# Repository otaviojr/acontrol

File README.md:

# acontrol
DIY Access Control Software - Fingerprint + NFC + Raspberry

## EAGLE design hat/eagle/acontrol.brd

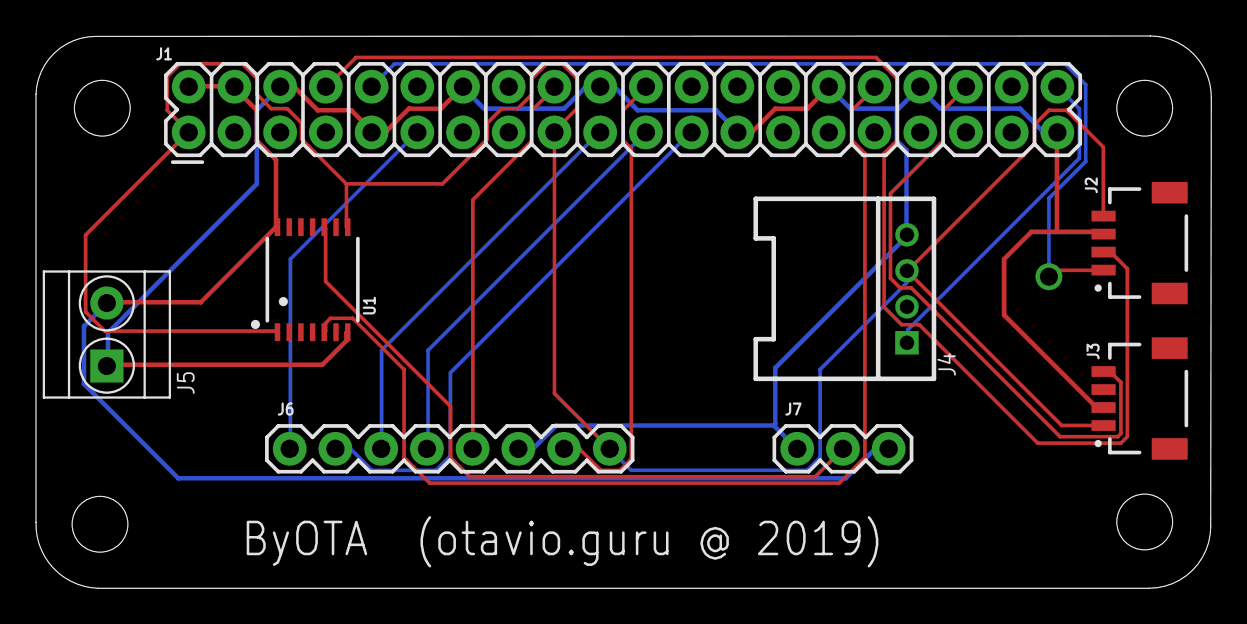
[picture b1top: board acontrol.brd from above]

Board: 2 copper layers, 65.3 x 30.7 mm, 8 parts (0 on the bottom side), 15 nets.

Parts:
J1: RASPBERRYPI-40-PIN-GPIO_PTH_NO_SHROUD; 2X20
J2, J3: JST04_1MM_RA
J4: 4P-2.0-90D; HW4-2.0-90D
J5: GREEN-2P-3.5; H2-3.5-7.0X7.0MM
J6: 1X08
J7: 455-1750-1-ND; 1X03
U1: TXB0104; TSSOP14

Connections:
3.3V: J1.1, J1.17, J2.4, J3.1, J4.3, J6.8, U1.1, U1.8
5V: J1.2, J1.4, J5.2, J7.3, U1.14
BUZZER_IN: J1.40, J4.1
GND: J1.6, J1.9, J1.14, J1.20, J1.25, J1.30, J1.34, J1.39, J2.3, J3.2, J4.4, J5.1, J6.6, J7.1, U1.7
GT_IPCCK: J1.36, J3.4
GT_RX: J1.8, J2.2
GT_TX: J1.10, J2.1
MFRC522_IRQ: J1.18, J6.5
MFRC522_MISO: J1.21, J6.4
MFRC522_MOSI: J1.19, J6.3
MFRC522_RESET: J1.22, J6.7
MFRC522_SCK: J1.23, J6.2
MFRC522_SDA: J1.11, J6.1
NEOPIXEL_IN: J1.32, U1.5
NEOPIXEL_OUT: J7.2, U1.10

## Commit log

2018-11-20 adding
2018-11-20 working
2018-11-21 programming web service endpoint
2018-11-25 audio driver
2018-11-25 sysfs delay on non root users
2018-11-25 improving
2018-11-26 mfrc522 programming
2018-11-27 PICC implementation
2018-11-27 implement IPCC commands
2018-12-02 working - MiFare read card
2018-12-02 working - MiFare Write
2018-12-03 working on read/write mfr522
2018-12-03 card workflow
2018-12-05 NFC methods programming
2018-12-05 cleaning code
2018-12-06 refactoring + persistence
2018-12-06 persistence driver
2018-12-07 persistence + NFC
2018-12-08 webservice + nfc reading, authorizing and restoring functions
2018-12-08 serde to json + yml
2018-12-09 webservice + persistence
2018-12-09 improvments
2018-12-10 workings webservices
2018-12-17 working on neopixel display
2018-12-17 neopixel device driver
2018-12-18 neopixel driver
2018-12-19 neopixel linux drivers
2018-12-19 neopixel linux driver
2018-12-20 netpixel linux driver
2018-12-21 neopixel kernel linux driver
2018-12-21 neopixel linux kernel driver
2018-12-24 linux kernel driver
2018-12-25 neolink linux kernel driver
2019-02-13 nepixel driver implementation
2019-02-13 cleaning
2019-02-14 neopixel animations
2019-02-17 neopixel animations + integrations
2019-02-18 audio/buzzer API
2019-03-03 command line client
2019-03-04 command line client app
2019-03-06 command line client tool
2019-03-07 fingerprint reader
2019-03-08 working on serial protocol witj fingerprint reader
2019-03-10 fingerprint driver
2019-03-20 fingerprint sensor
2019-03-21 fingerprint animations feedback
2019-03-22 fingerprint animations
2019-03-23 finterprint reading + enrolling + animations
2019-03-23 buzzer kernel driver to use pcm to driver a piezo buzzer
2019-03-26 pcm driver working
2019-03-27 buzzer kernel driver
2019-03-27 buzzer kernel device driver
2019-03-28 buzzer kernel pcm driver
2019-03-30 Buzzer kernel driver - working
2019-04-01 buzzer pcm kernel driver
2019-04-01 buzzer PCM kernel module
2019-04-01 file headers + formating
2019-04-01 implementing some musics to play on buzzer
2019-04-02 supermario theme
2019-04-02 working on animations and sound effects
2019-04-02 formating
2019-04-03 sound thread improvments
2019-04-07 cleaning...
2019-04-08 improving fingerprint reader...
2019-04-21 docs
2019-04-21 Set theme jekyll-theme-hacker
2019-04-21 github pages
2019-04-22 changing template
2019-05-17 raspberry pi zero dts
2019-05-19 hardware - Raspberry Pi Zero W uHat
2019-06-21 Raspberry pi Zero adjustments
2019-07-01 uHat corrections + 3D printed case
2019-07-07 Dependencies adjustments granted/denieded scripts on threads
2019-07-07 cleanning logs
2019-10-26 trait without dyn deprecated
2019-10-26 no need for mut
2019-10-26 overlays
2019-11-02 Bump nokogiri from 1.10.2 to 1.10.5 in /docs
    Bumps [nokogiri](https://github.com/sparklemotion/nokogiri) from 1.10.2 to 1.10.5.
    - [Release notes](https://github.com/sparklemotion/nokogiri/releases)
    - [Changelog](https://github.com/sparklemotion/nokogiri/blob/master/CHANGELOG.md)
    - [Commits](https://github.com/sparklemotion/nokogiri/compare/v1.10.2...v1.10.5)
2019-11-11 working pn532
2019-11-11 pn532
2019-11-23 fixing things
2020-01-17 optimizations
2020-01-17 echoing output
2020-02-25 Bump nokogiri from 1.10.2 to 1.10.8 in /docs
    Bumps [nokogiri](https://github.com/sparklemotion/nokogiri) from 1.10.2 to 1.10.8.
    - [Release notes](https://github.com/sparklemotion/nokogiri/releases)
    - [Changelog](https://github.com/sparklemotion/nokogiri/blob/master/CHANGELOG.md)
    - [Commits](https://github.com/sparklemotion/nokogiri/compare/v1.10.2...v1.10.8)
2021-05-20 Bump nokogiri from 1.10.2 to 1.11.4 in /docs
    Bumps [nokogiri](https://github.com/sparklemotion/nokogiri) from 1.10.2 to 1.11.4.
    - [Release notes](https://github.com/sparklemotion/nokogiri/releases)
    - [Changelog](https://github.com/sparklemotion/nokogiri/blob/main/CHANGELOG.md)
    - [Commits](https://github.com/sparklemotion/nokogiri/compare/v1.10.2...v1.11.4)
2021-07-13 Bump addressable from 2.5.2 to 2.8.0 in /docs
    Bumps [addressable](https://github.com/sporkmonger/addressable) from 2.5.2 to 2.8.0.
    - [Release notes](https://github.com/sporkmonger/addressable/releases)
    - [Changelog](https://github.com/sporkmonger/addressable/blob/main/CHANGELOG.md)
    - [Commits](https://github.com/sporkmonger/addressable/compare/addressable-2.5.2...addressable-2.8.0)
    ---
    updated-dependencies:
2021-09-27 Bump nokogiri from 1.10.2 to 1.12.5 in /docs
    Bumps [nokogiri](https://github.com/sparklemotion/nokogiri) from 1.10.2 to 1.12.5.
    - [Release notes](https://github.com/sparklemotion/nokogiri/releases)
    - [Changelog](https://github.com/sparklemotion/nokogiri/blob/main/CHANGELOG.md)
    - [Commits](https://github.com/sparklemotion/nokogiri/compare/v1.10.2...v1.12.5)
    ---
    updated-dependencies:
2022-02-26 Bump nokogiri from 1.10.2 to 1.13.3 in /docs
    Bumps [nokogiri](https://github.com/sparklemotion/nokogiri) from 1.10.2 to 1.13.3.
    - [Release notes](https://github.com/sparklemotion/nokogiri/releases)
    - [Changelog](https://github.com/sparklemotion/nokogiri/blob/main/CHANGELOG.md)
    - [Commits](https://github.com/sparklemotion/nokogiri/compare/v1.10.2...v1.13.3)
    ---
    updated-dependencies:
2022-04-12 Bump nokogiri from 1.10.2 to 1.13.4 in /docs
    Bumps [nokogiri](https://github.com/sparklemotion/nokogiri) from 1.10.2 to 1.13.4.
    - [Release notes](https://github.com/sparklemotion/nokogiri/releases)
    - [Changelog](https://github.com/sparklemotion/nokogiri/blob/v1.13.4/CHANGELOG.md)
    - [Commits](https://github.com/sparklemotion/nokogiri/compare/v1.10.2...v1.13.4)
    ---
    updated-dependencies:
2022-05-18 Bump nokogiri from 1.10.2 to 1.13.6 in /docs
    Bumps [nokogiri](https://github.com/sparklemotion/nokogiri) from 1.10.2 to 1.13.6.
    - [Release notes](https://github.com/sparklemotion/nokogiri/releases)
    - [Changelog](https://github.com/sparklemotion/nokogiri/blob/main/CHANGELOG.md)
    - [Commits](https://github.com/sparklemotion/nokogiri/compare/v1.10.2...v1.13.6)
    ---
    updated-dependencies:
2022-07-22 Bump tzinfo from 1.2.5 to 1.2.10 in /docs
    Bumps [tzinfo](https://github.com/tzinfo/tzinfo) from 1.2.5 to 1.2.10.
    - [Release notes](https://github.com/tzinfo/tzinfo/releases)
    - [Changelog](https://github.com/tzinfo/tzinfo/blob/master/CHANGES.md)
    - [Commits](https://github.com/tzinfo/tzinfo/compare/v1.2.5...v1.2.10)
    ---
    updated-dependencies:
2022-09-16 cleanning warnings
2022-09-16 Bump rubyzip from 1.2.2 to 2.3.2 in /docs
    Bumps [rubyzip](https://github.com/rubyzip/rubyzip) from 1.2.2 to 2.3.2.
    - [Release notes](https://github.com/rubyzip/rubyzip/releases)
    - [Changelog](https://github.com/rubyzip/rubyzip/blob/master/Changelog.md)
    - [Commits](https://github.com/rubyzip/rubyzip/compare/v1.2.2...v2.3.2)
    ---
    updated-dependencies:
2022-09-16 cleanning
2022-09-16 version bump
2022-09-17 Edition 2018 + bluez
2022-09-17 cross + bluetooth
2022-09-18 working..
2022-09-19 bluetooth
2022-09-19 bluetooth + mobile
2022-09-19 mobile
2022-09-24 clean
2022-09-25 icons
2022-09-26 splash test
2022-09-26 splash
2022-09-26 no allow mobile phone screen to turn off
2022-09-26 iOS icons
2022-09-26 screen lock
2022-09-29 logs
2022-09-29 improvements + new log system
2022-09-30 improvements
2022-10-01 android
2022-10-02 android icons
2022-10-02 file log implementation
2023-09-18 kikad project + 24VAC spice

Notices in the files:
parts and their libraries:
SparkFun-Connectors: Licensing: Creative Commons ShareAlike 4.0 International - https://creativecommons.org/licenses/by-sa/4.0
